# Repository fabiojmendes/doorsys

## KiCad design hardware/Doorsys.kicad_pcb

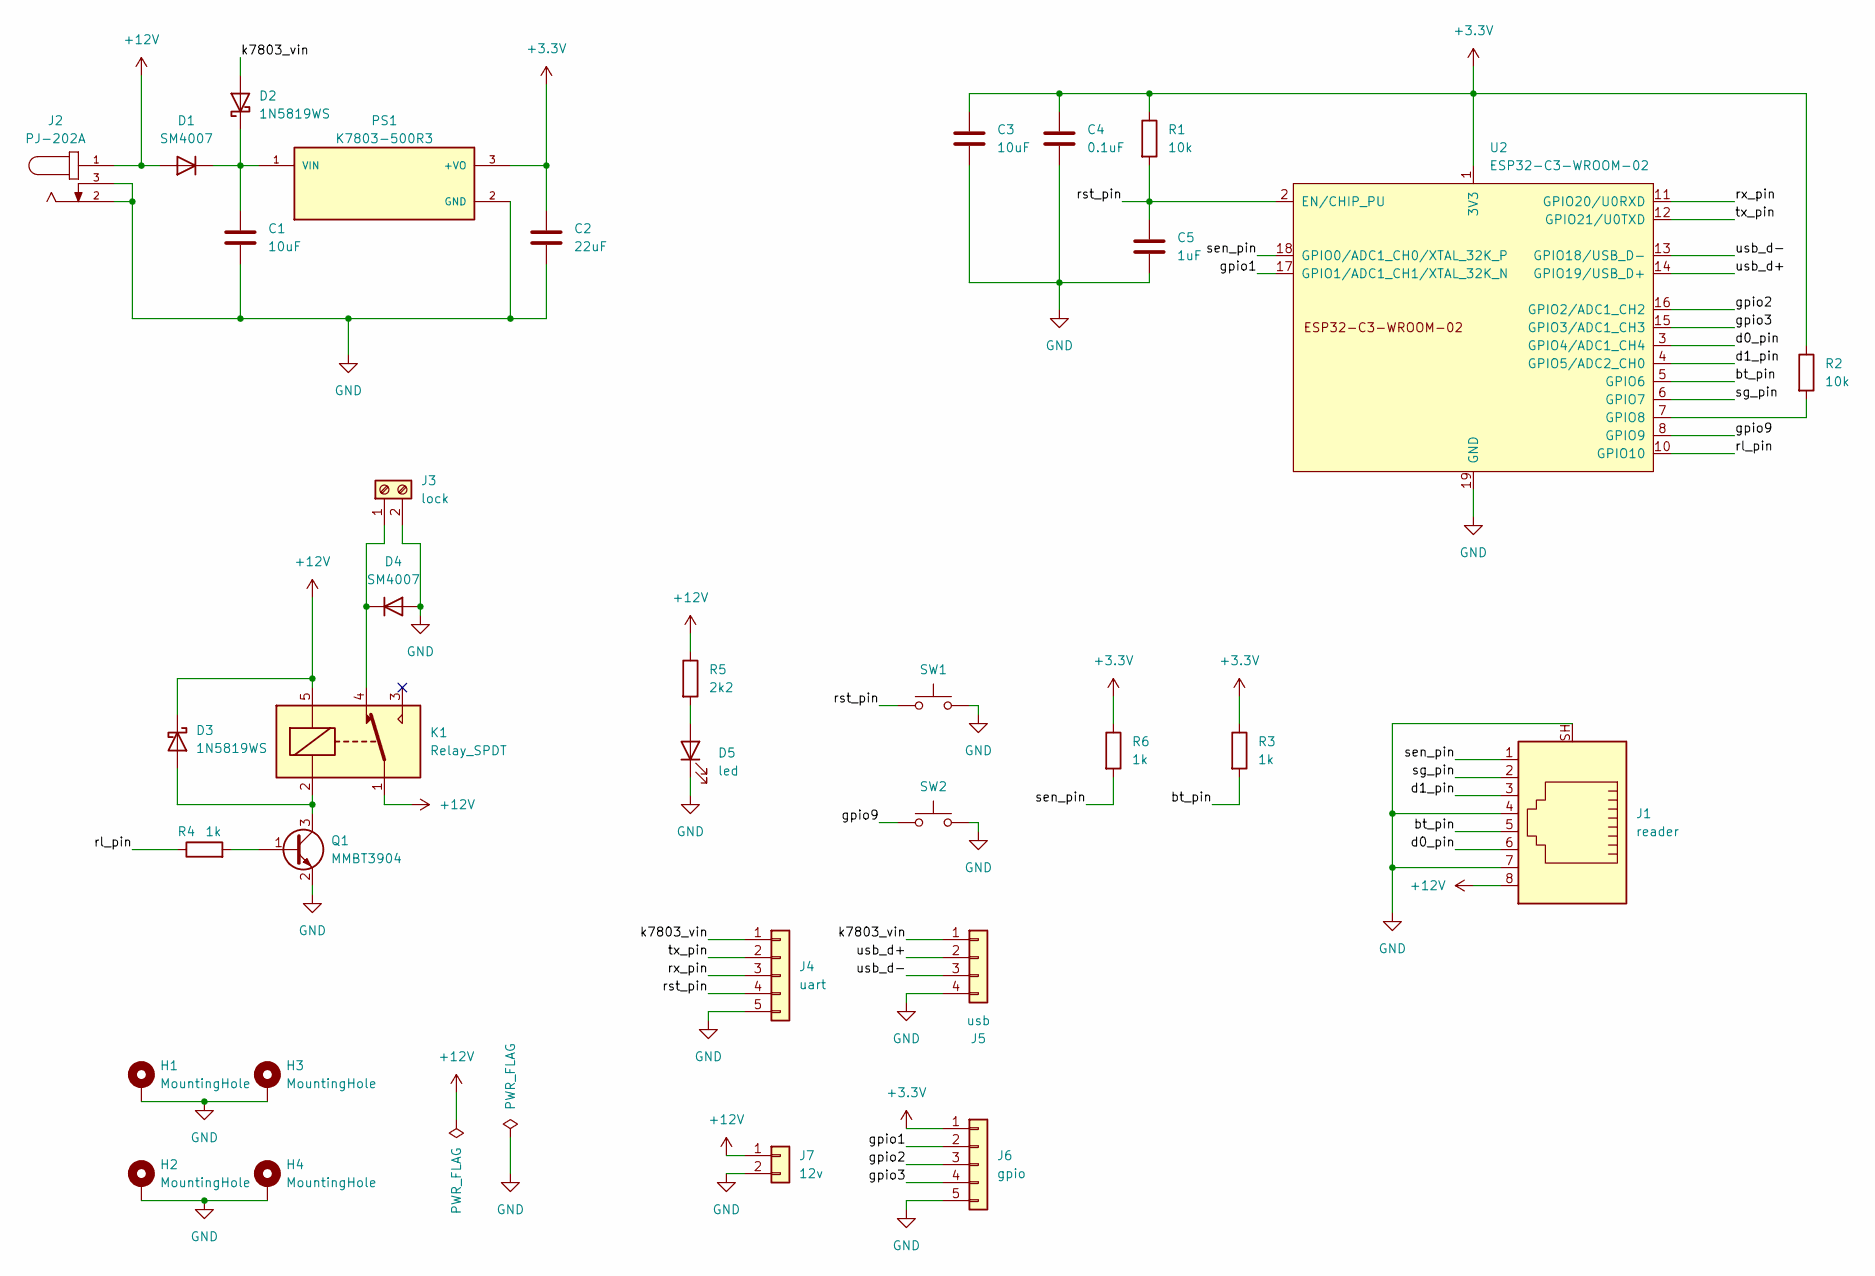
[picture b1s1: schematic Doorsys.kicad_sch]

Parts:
C1: 10uF; C_1206_3216Metric; LCSC C13585
C2: 22uF; C_0805_2012Metric; LCSC C45783
C3: 10uF; C_0805_2012Metric; LCSC C15850
C4: 0.1uF; C_0805_2012Metric; LCSC C28233
C5: 1uF; C_0805_2012Metric; LCSC C28323
D1, D4: SM4007; D_SOD-123F; LCSC C64898
D2, D3: 1N5819WS; D_SOD-323; LCSC C191023
D5: led; LED_0805_2012Metric; LCSC C2297
H1, H2, H3, H4: MountingHole; MountingHole_2.2mm_M2_ISO7380_Pad
J1: reader; CONN8_2-908LF_AMP
J2: PJ-202A; CUI_PJ-202A
J3: lock; CONN_1935161_PXC
J4: uart; PinHeader_1x05_P2.54mm_Vertical
J5: usb; PinHeader_1x04_P2.54mm_Vertical
J6: gpio; PinHeader_1x05_P2.54mm_Vertical
J7: 12v; PinHeader_1x02_P2.54mm_Vertical
K1: Relay_SPDT; Relay_SPDT_Omron-G5LE-1
PS1: K7803-500R3; CONV_K7803-500R3; PARTREV 2020.12.17-A/7
Q1: MMBT3904; SOT-23; LCSC C20526
R1, R2: 10k; R_0805_2012Metric; LCSC C17414
R3, R4, R6: 1k; R_0805_2012Metric; LCSC C17513
R5: 2k2; R_0805_2012Metric; LCSC C17520
SW1, SW2: SW_Push_1P1T_XKB_TS-1187A; LCSC C318884
U2: ESP32-C3-WROOM-02

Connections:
+3.3V: C2.1, C3.1, C4.1, J6.1, PS1.3 (+VO), R1.1, R2.1, R3.1, R6.1, U2.1 (3V3)
+12V: D1.2 (A), D3.1 (K), J1.8, J2.1, J7.1, K1.1, K1.5, R5.1
/bt_pin: J1.5, R3.2, U2.5 (GPIO6)
/d0_pin: J1.6, U2.3 (GPIO4/ADC1_CH4)
/d1_pin: J1.3, U2.4 (GPIO5/ADC2_CH0)
/gpio1: J6.2, U2.17 (GPIO1/ADC1_CH1/XTAL_32K_N)
/gpio2: J6.3, U2.16 (GPIO2/ADC1_CH2)
/gpio3: J6.4, U2.15 (GPIO3/ADC1_CH3)
/gpio9: SW2.1, U2.8 (GPIO9)
/k7803_vin: D2.2 (A), J4.1, J5.1
/rl_pin: R4.1, U2.10 (GPIO10)
/rst_pin: C5.1, J4.4, R1.2, SW1.1, U2.2 (EN/CHIP_PU)
/rx_pin: J4.3, U2.11 (GPIO20/U0RXD)
/sen_pin: J1.1, R6.2, U2.18 (GPIO0/ADC1_CH0/XTAL_32K_P)
/sg_pin: J1.2, U2.6 (GPIO7)
/tx_pin: J4.2, U2.12 (GPIO21/U0TXD)
/usb_d+: J5.2, U2.14 (GPIO19/USB_D+)
/usb_d-: J5.3, U2.13 (GPIO18/USB_D-)
GND: C1.2, C2.2, C3.2, C4.2, C5.2, D4.2 (A), D5.1 (K), H1.1, H2.1, H3.1, H4.1, J1.4, J1.7, J1.SH, J2.2, J2.3, J3.2, J4.5, J5.4, J6.5, J7.2, PS1.2 (GND), Q1.2 (E), SW1.2, SW2.2, U2.9 (GND), U2.19 (GND)
unnamed: C1.1, D1.1 (K), D2.1 (K), PS1.1 (VIN)
unnamed: D3.2 (A), K1.2, Q1.3 (C)
unnamed: D4.1 (K), J3.1, K1.4
unnamed: D5.2 (A), R5.2
unnamed: Q1.1 (B), R4.2
unnamed: R2.2, U2.7 (GPIO8)

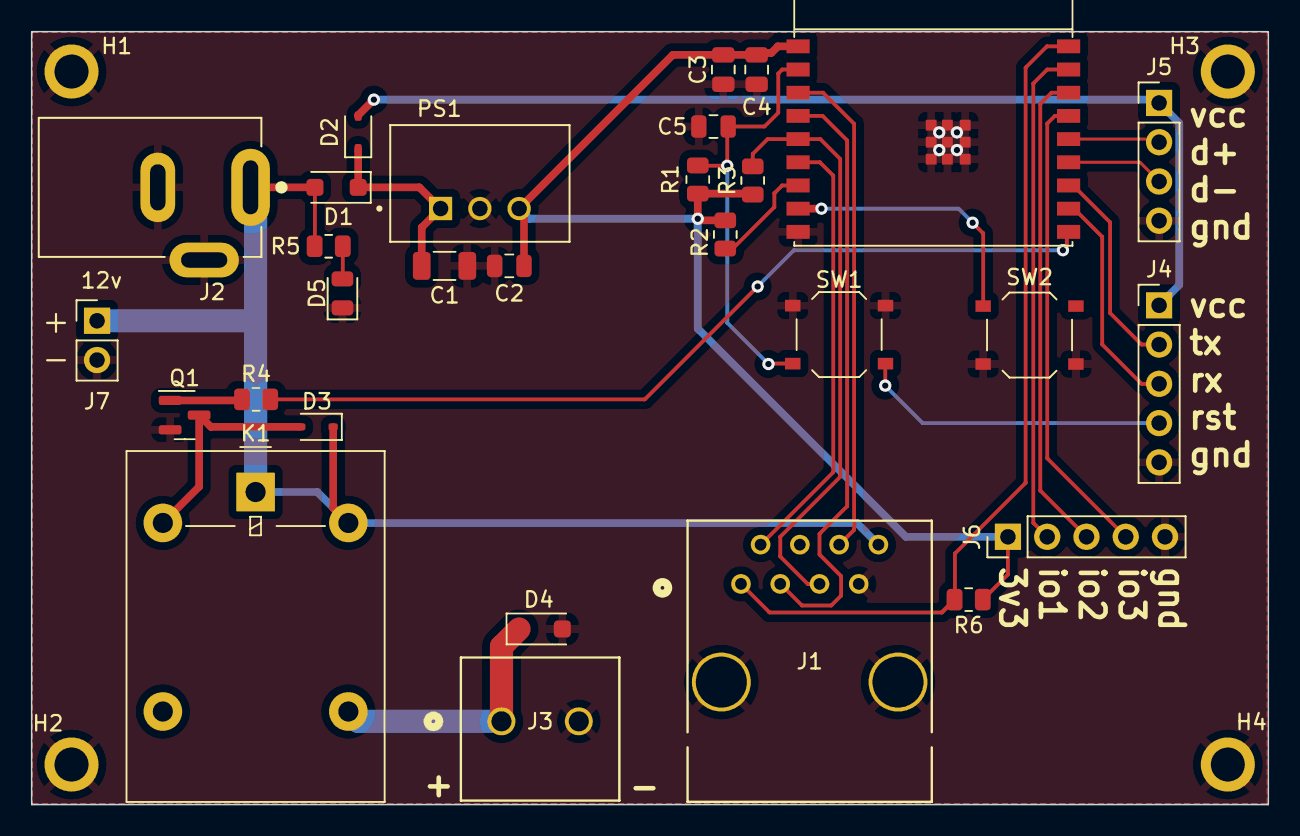
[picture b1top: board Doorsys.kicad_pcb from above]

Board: 2 copper layers, 80.0 x 50.0 mm, 33 parts (0 on the bottom side), 25 nets.

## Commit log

2023-08-25 Publish to github
2023-08-26 Implmenting parity check for wiegand protocol
2023-08-27 Extending the heap information
2023-08-29 Extracting the protocol into its own library and using bincode
2023-08-30 Change code to string
2023-08-30 Adding cli project to interact with mqtt
2023-09-23 Api implementation for users and codes
2023-09-24 Adding update endpoints
2023-09-24 Removing admin module
2023-09-30 First pass on the api
2023-09-30 Adding the vuejs webui
2023-10-02 Renaming users to customers
2023-10-03 StaffList component
2023-10-03 Adding the staff list and setting the max-width
2023-10-03 StaffView & StaffList improvements. EntryLog touch up
2023-10-06 Changed navbar behavior
2023-10-07 Adding staff api
2023-10-07 Dependency management
2023-10-08 Fixing the router
2023-10-08 Adding the code type and making fob unique
2023-10-10 Adding mqtt
2023-10-15 Testing mqtt
2023-10-16 Using raw strings for queries
2023-10-16 Updating mqtt lib
2023-10-16 Cosmetic update
2023-10-23 Updating esp32 to esp-idf-svc 0.47.1
2023-10-24 Migrating to esp32 chip
2023-10-25 Changed to at least once delivery
2023-10-28 Adding UserDB class to handle codes
2023-11-05 Changing code and fob datatype to int
2023-11-06 Processing multipart mqtt messages
2023-11-07 Adding nvs stats
2023-11-07 Change the pin range to be inclusive
2023-11-11 Adding error messages
2023-11-19 Improving button interrupt
2023-11-27 Adding retry for mqtt connection
2023-11-27 Adding mqtt config url
2023-11-27 Removing dead code
2023-11-27 Adding docker build to webapp
2023-11-27 Upgrading axum
2023-11-27 Api docker build and sqlx prep
2023-11-27 Fixing notes formatting
2023-11-27 Remove hardcoded url
2023-11-28 Fixing secret name
2023-11-28 Another attempt with build env
2023-11-28 Fix checkout
2023-11-28 Adding build args
2023-11-28 Updating favicon
2023-11-28 Remove unused env var
2023-12-06 Using exactly once for audit delivery
2023-12-18 Migrating back to esp32-c3
2023-12-18 Limiting the number of results on entry logs
2023-12-18 Adding kicad files
2024-01-09 Increasing the mqtt outbox retation to 24hrs
2024-01-10 Adding staff status api
2024-01-10 Update sqlx query cache
2024-01-10 Change rumqttc version
2024-01-11 Deactivate function
2024-01-11 Resubscribe to topics when disconnected
2024-01-11 Using publish to avoid messages being stored
2024-01-11 Removing hardcoded addresses
2024-01-11 Adding logs config
2024-01-12 Log fix
2024-01-13 Change the QOS for audit messages to AtLeastOnce
2024-01-18 Adding keypad feedback
2024-01-19 Using unique identifier based on mac address and hostname
2024-01-19 Adding bulk load of codes
2024-01-21 Rollback to WPA2Personal
2024-02-12 Moving api to a path instead of subdomain
2024-07-19 Introducing device id
2024-07-19 Backwards compatibility adjustment
2024-07-20 Adding date filter capability
2024-07-20 Fix sqlx cache
2024-07-20 Change default filter
2024-07-21 Adding customer fiter
2024-07-21 Sorting customers by name
2024-07-21 No results found message
2024-07-21 Change entry display format
2024-07-21 Fix default value for date field and remove limit on entry log results
2024-07-23 Renaming to net_id
2024-07-23 Adding pre commit hook
2024-07-23 Polish
2024-07-23 Update pre-commit hook2
2024-07-24 Adding graceful shutdown hook
2024-07-25 Change docker build for api
2024-07-25 Update docker build
2024-07-25 Update entrypoint script
2024-07-25 Adding startup logs
2024-07-25 Adjusting timings
2024-07-26 Display door
2024-07-27 Healthcheck
2024-07-27 Update healthcheck command
2024-07-27 Remove healthcheck from image
2024-07-27 Improving logs
2024-07-27 Modify logs
2024-07-27 Modify env variables
2024-07-28 Fix RUST_LOG envvar
2024-07-28 Add min connections
2024-07-29 Adding device list api
2024-07-29 Adding labels to the docker image
2024-07-29 Adding filter by device
2024-07-29 Adding custom log formatter
2024-07-29 Revert "Adding custom log formatter"
    This reverts commit 79ae217c2f1ac6d11679b9095a5950e1054b3f6d.
2024-07-31 Revert: Adding custom formatter back
    This reverts commit 18134c6ea73f75ea1eefeae3f19a96406ade57cd.
2024-07-31 Adjusting priority map
2024-07-31 Updating api versions
2024-07-31 Updating webapp versions
2024-07-31 Adding global error handling
2024-08-01 Renaming sql migrations
2024-08-01 Adding customer active status
2024-08-01 Adding customer active status web
2024-08-01 Adding staff service
2024-08-01 Update staff view after bulk action
2024-08-05 Adding toast notifications
2024-08-05 Handling bulk deactivations
2024-08-08 Fixing build issues
2024-08-08 Upgrading to esp-idf-svc 0.49
2024-08-08 Adding work-around for rust-analyzer
2024-08-08 Fix clippy report
2024-08-19 Updating to kicad 8.0
2024-08-19 Polishing
2024-08-19 Adding build information at runtime
